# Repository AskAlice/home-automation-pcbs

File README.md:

# home-automation-pcbs

Open-hardware IoT boards for home automation, designed for **ESPHome** and/or
**Matter-over-Thread / Zigbee** (ESP32-C3/C6/S3/H2 based). All projects are
native **KiCad 8** and fully self-contained (project-local symbol libraries,
inline custom footprints, generator scripts — every file is reproducible).

> ⚠ **Verify before fabrication.** Footprints for ESP modules and sensors are
> drawn from published datasheets but these boards have not been through a
> physical run. v0.1 boards have signal routing left for autorouting
> (documented per-board). Check each board README before ordering PCBs.
> **RelayMini contains mains voltage — read its safety section first.**

## Boards

| Board | MCU | Ecosystem | Function | Status |
|---|---|---|---|---|
| [`boards/sensenode-c6`](boards/sensenode-c6) | ESP32-C6-WROOM-1 | ESPHome (Wi-Fi) + Matter/Thread | Temp/hum, lux, pressure, PIR | v0.1 routed (power), partial ratsnest |
| [`boards/presencepro-c3`](boards/presencepro-c3) | ESP32-C3-WROOM-02 | ESPHome | HLK-LD2410 mmWave presence + lux | v0.1 |
| [`boards/ledquad-c3`](boards/ledquad-c3) | ESP32-C3-WROOM-02 | ESPHome / WLED | 4-ch 12–24 V PWM LED driver | v0.1 |
| [`boards/relaymini-c3`](boards/relaymini-c3) | ESP32-C3-WROOM-02 | ESPHome | ⚠ Mains switch + BL0942 metering | v0.1, safety gates green |
| [`boards/ledhub-c6`](boards/ledhub-c6) | ESP32-C6-WROOM-1 | WLED / ESPHome | 2.8" TFT all-in-one LED controller | v0.1 (flagship) |
| [`boards/threadnode-h2`](boards/threadnode-h2) | ESP32-H2-MINI-1 | Matter-over-Thread / Zigbee | Battery contact sensor / button | v0.1 concept |
| [`boards/airquality-s3`](boards/airquality-s3) | ESP32-S3-WROOM-1 | ESPHome | CO₂ + VOC + temp/hum + OLED header | v0.1 concept |
| [`boards/blinddriver-c6`](boards/blinddriver-c6) | ESP32-C6-WROOM-1 | ESPHome / Matter | TMC2209 roller-blind controller | v0.1 concept |
| [`boards/irblaster-c3`](boards/irblaster-c3) | ESP32-C3-WROOM-02 | ESPHome | IR TX/RX climate bridge | v0.1 concept |
| [`boards/gardenprobe-c6`](boards/gardenprobe-c6) | ESP32-C6-WROOM-1 | ESPHome / Matter | Battery soil-moisture probe | v0.1 concept |
| [`boards/threadrcp-h2`](boards/threadrcp-h2) | ESP32-H2-MINI-1 | OpenThread RCP / Zigbee NCP | Border-router USB dongle | v0.1 concept |
| [`boards/garagepilot-c6`](boards/garagepilot-c6) | ESP32-C6-WROOM-1 | ESPHome | Garage-door relay + 3× inputs | v0.1 routed, DRC/ERC issues |

Each board folder contains: `*.kicad_pro/.kicad_sch/.kicad_pcb`, project-local
symbol library, `bom_lcsc.csv` (real, in-stock LCSC part numbers), `README.md`
(BOM, pinout, flashing, analyzer notes), `esphome/*.yaml`, render PNGs, and the
generator script (`gen_*.py`).

## Board showcase

### 🌡️ [SenseNode C6](boards/sensenode-c6) — environmental multisensor

One-per-room environmental node. ESP32-C6 gives you Wi-Fi 6 + BLE5 **and**
802.15.4, so the same SKU can run ESPHome today and Matter-over-Thread tomorrow.

- **Sensors:** SHT31 (temp/hum), BH1750 (lux), BMP280 (pressure), AM312 PIR (motion)
- **Power:** USB-C 5 V → AP2112K-3.3 LDO; EN/BOOT buttons; 1×4 prog header
- **Key parts:** ESP32-C6-WROOM-1, SHT31-AD1B, BH1750FVI, BMP280, AP2112K-3.3, USB-C 16P
- **Firmware:** `boards/sensenode-c6/esphome/sensenode-c6.yaml` (+ esp-matter note)

| Function | ESP32-C6 GPIO |
|---|---|
| I2C SDA / SCL (SHT31 + BH1750 + BMP280) | 6 / 7 |
| PIR OUT (J1) | 4 |
| Status LED (active low) | 8 |
| BOOT button | 9 |
| USB D− / D+ | 12 / 13 |
| UART0 TX0 / RX0 (prog header) | 16 / 17 |
| EN reset | EN |

---

### 🚶 [PresencePro C3](boards/presencepro-c3) — mmWave presence + lux

True still-presence detection (sitting at a desk, sleeping) where PIR fails,
with lux gating so automations only fire when it's dark.

- **Sensors:** HLK-LD2410(B) 24 GHz mmWave (moving + static targets, configurable
  gates), BH1750 ambient light
- **Power:** USB-C 5 V → AP2112K-3.3; native USB flashing
- **Key parts:** ESP32-C3-WROOM-02, HLK-LD2410B (module on 1×5 header), BH1750FVI, AP2112K
- **Firmware:** `esphome/presencepro-c3.yaml` (native `ld2410` component)

| Function | ESP32-C3 GPIO |
|---|---|
| Radar UART RX / TX | 4 / 5 |
| Radar OUT (occupancy) | 3 |
| I2C SDA / SCL (BH1750) | 6 / 7 |
| USB D− / D+ | 18 / 19 |
| Status LED | 10 |
| BOOT / EN | 9 / EN |
| UART0 RX0 / TX0 (prog) | 20 / 21 |

---

### 💡 [LEDQuad C3](boards/ledquad-c3) — 4-ch 12–24 V PWM LED driver

Analog RGBW strip driver for 12/24 V strips — the classic ESPHome `light.rgbw`
board, sized to hide behind furniture.

- **Outputs:** 4× AO3400A N-MOSFET low-side channels on 5.08 mm screw terminals
- **Power:** 12–24 V in (fused) → AP63205 buck 5 V/2 A → AP2112 3.3 V; USB-C
  programming diode-OR'd with the buck rail
- **Key parts:** ESP32-C3-WROOM-02, AP63205, AP2112K-3.3, 4× AO3400A, SS34, USB-C 16P
- **Firmware:** `esphome/ledquad-c3.yaml` (also WLED-friendly)

| Function | ESP32-C3 GPIO |
|---|---|
| PWM R / G / B / W | 4 / 5 / 6 / 7 |
| Status LED | 10 |
| BOOT button | 9 |
| USB D− / D+ | 18 / 19 |
| UART0 TX0 / RX0 | 21 / 20 |
| EN reset | EN |

---

### 🔌 [RelayMini C3](boards/relaymini-c3) — mains switch + energy metering

> ⚠ **110–240 VAC mains board. Lethal voltages. Qualified builders only —
> read the safety section in its README before anything else.**

Sonoff-Basic-class inline switch, but with proper engineering: fused input,
isolation slot, opto-isolated metering, and a SELV-side programming header.

- **Switching:** HF32F-G relay 10 A/250 VAC, 10 A fuse, MOV, creepage ≥ 6 mm,
  milled isolation slot between mains and SELV domains
- **Metering:** BL0942 (V/A/W/Wh/PF) with PC817 opto-isolated UART
- **Key parts:** ESP32-C3-WROOM-02, HLK-PM01 AC/DC, HF32F-G, BL0942, PC817 ×2
- **Firmware:** `esphome/relaymini-c3.yaml` (`bl0942` component)

| Function | GPIO |
|---|---|
| Relay driver (→ K1 coil) | GPIO6 |
| BL0942 UART RX / TX | GPIO4 / GPIO5 |
| User button (active low) | GPIO9 |
| Status LED (active low) | GPIO8 |
| Prog header (SELV side only!) TX0/RX0 | GPIO21 / GPIO20 |

---

### 🕹️ [LEDHub C6](boards/ledhub-c6) — all-in-one display LED controller (flagship)

A complete addressable-LED control station: status display, physical controls,
presence-aware switching and environmental telemetry, running **WLED** with a
custom usermod (`firmware/wled-usermod-ledhub`).

- **Display/UI:** 2.8" ILI9341 TFT (effect, palette, brightness, IP, RSSI),
  EC11 rotary encoder, 5-way nav buttons on one ADC pin (resistor ladder)
- **Sensors:** SHT31 + BH1750 (I2C), INMP441 I2S mic, LD2450 mmWave radar header
- **Output:** WS2812 data via 74AHCT125 level shifter + 470 Ω; separate 5 V LED
  power terminal
- **Key parts:** ESP32-C6-WROOM-1, 74AHCT125, INMP441, SHT31, BH1750, EC11, AP2112K
- **Firmware:** WLED usermod + `esphome/ledhub-c6.yaml`

| Function | ESP32-C6 GPIO |
|---|---|
| TFT SCK / MOSI / CS / DC / RST / BL | 6 / 7 / 5 / 4 / 1 / 2 |
| Encoder A / B | 15 / 16 |
| Nav button ladder (ADC) | 0 |
| INMP441 I2S SCK / WS / SD | 17 / 18 / 19 |
| I2C SDA / SCL | 20 / 21 |
| LD2450 radar RX / TX | 22 / 23 |
| WS2812 data (→ 74AHCT125) | 3 |
| USB D− / D+ | 12 / 13 |

---

### 🚪 [ThreadNode H2](boards/threadnode-h2) — battery Thread contact/button node

ESP32-H2 = 802.15.4 only, built for deep sleep: a CR2032 door/window sensor or
smart button on a Matter-over-Thread or Zigbee network.

- **Power:** CR2032 direct (no LDO — brown-out note in README); reed-switch
  deep-sleep wakeup
- **Key parts:** ESP32-H2-MINI-1, CR2032 holder, reed/header input, 4.7k I2C pull-ups
- **Firmware:** Matter-over-Thread via esp-matter (note in README)

| Signal | GPIO | Notes |
|---|---|---|
| REED | GPIO3 | reed switch to GND, deep-sleep wakeup |
| I2C SDA / SCL | GPIO12 / GPIO13 | expansion header |
| STAT LED | GPIO8 | pulse only — battery |
| BTN (BOOT) | GPIO9 | user button / ROM bootloader |
| TX0 / RX0 | GPIO24 / GPIO23 | prog header (no USB) |

---

### 🌫️ [AirQuality S3](boards/airquality-s3) — CO₂ / VOC / temp / humidity

Full indoor-air-quality node with photoacoustic CO₂ and metal-oxide VOC on one
I2C bus, plus a header for a 0.96" SSD1306 OLED readout.

- **Sensors:** Sensirion SCD40 (CO₂), SGP40 (VOC index), SHT40 (temp/hum)
- **Key parts:** ESP32-S3-WROOM-1, SCD40, SGP40, SHT40, AP2112K-3.3, USB-C
- **Firmware:** `esphome/airquality-s3.yaml` (`scd4x`, `sgp40`, `sht4x`)

| Signal | GPIO | Notes |
|---|---|---|
| I2C SDA / SCL | GPIO8 / GPIO9 | SCD40 0x62, SGP40 0x59, SHT40 0x44, OLED 0x3C |
| BOOT / RST | GPIO0 / EN | |
| STAT LED | GPIO38 | |
| USB D− / D+ | GPIO19 / GPIO20 | native USB flashing |
| TX0 / RX0 | GPIO43 / GPIO44 | spare UART |

---

### 🪟 [BlindDriver C6](boards/blinddriver-c6) — TMC2209 roller-blind controller

Quiet Trinamic stepper control for roller blinds, with ESPHome `cover`
semantics and Wi-Fi 6 + Thread on tap.

- **Driver:** TMC2209 socket (STEP/DIR/EN/DIAG + 1-wire UART config),
  end-stop header, 12 V VMOT with SS34 reverse-polarity protection
- **Power chain:** 12 V → AP63205 5 V → AP2112 3.3 V
- **Key parts:** ESP32-C6-WROOM-1, TMC2209, AP63205, screw terminals
- **Firmware:** `esphome/blinddriver-c6.yaml` (stepper cover)

| Signal | GPIO | Notes |
|---|---|---|
| STEP / DIR | GPIO4 / GPIO5 | TMC2209 socket |
| TMC_EN / DIAG | GPIO6 / GPIO7 | |
| TMC_UART | GPIO15 | 1-wire PDN_UART config |
| ENDSTOP | GPIO18 | header, pull-up |
| USB D− / D+ | GPIO12 / GPIO13 | |

---

### 📡 [IRBlaster C3](boards/irblaster-c3) — IR climate bridge

Give any dumb IR AC/heater a brain: ESPHome `climate_ir` with transmit and
receive (learn your remote's codes).

- **TX:** 2× TSAL6200 high-power IR LEDs driven by S8050 (GPIO4)
- **RX:** TSOP38238 38 kHz receiver (GPIO5); optional BH1750 lux on I2C
- **Key parts:** ESP32-C3-WROOM-02, TSAL6200 ×2, TSOP38238, S8050, BH1750
- **Firmware:** `esphome/irblaster-c3.yaml` (`remote_transmitter`/`remote_receiver`)

| Signal | GPIO | Notes |
|---|---|---|
| IR_TX | GPIO4 | → S8050 → 2× TSAL6200 |
| IR_RX | GPIO5 | TSOP38238 out |
| I2C SDA / SCL | GPIO6 / GPIO7 | BH1750 0x23 |
| STAT LED / BOOT | GPIO10 / GPIO9 | |
| USB D− / D+ | GPIO18 / GPIO19 | |

---

### 🌱 [GardenProbe C6](boards/gardenprobe-c6) — battery soil-moisture stick

Plant sensor built as a 70 × 25 mm stick: the probe is the PCB — a capacitive
copper area on the bottom tip, corrosion-free versus resistive probes.

- **Sensing:** capacitive fixed-RC probe (GPIO0/1), SHT31 on a load-switched
  rail (AO3401) to save battery, 100k/100k battery divider
- **Power:** 3.7 V LiPo on JST-PH, MCP1700-3302 LDO (charge externally)
- **Key parts:** ESP32-C6-WROOM-1, MCP1700, AO3401, SHT31
- **Firmware:** `esphome/gardenprobe-c6.yaml` (deep sleep)

| Signal | GPIO | Notes |
|---|---|---|
| SOIL_ADC / SOIL_CHG | GPIO0 / GPIO1 | capacitive probe |
| BATT_ADC | GPIO2 | Vbat/2 divider |
| LOAD_EN | GPIO3 | sensor rail load switch |
| I2C SDA / SCL | GPIO20 / GPIO21 | SHT31 0x44 |
| TX0 / RX0 | GPIO16 / GPIO17 | prog header (no USB) |

---

### 🧵 [ThreadRCP H2](boards/threadrcp-h2) — OpenThread border-router dongle

35 × 20 mm USB-C dongle that turns a Home Assistant box into an OpenThread
Border Router — the missing piece for all the H2/C6 Thread boards above.

- **Function:** ESP32-H2 RCP firmware (`esp_ot_br` / ot-rcp), native USB
  transport (GPIO26/27) — no UART bridge chip
- **Layout:** module rotated so the antenna overhangs the board edge
  (metal-free keep-out marked on silk)
- **Key parts:** ESP32-H2-MINI-1, USB-C 16P, AP2112K-3.3
- **Firmware:** Espressif ot_rcp example (flash command in README)

| Signal | GPIO | Notes |
|---|---|---|
| USB D− / D+ | GPIO26 / GPIO27 | RCP transport |
| STAT LED | GPIO8 | |
| BOOT / RST | GPIO9 / EN | |
| TX0 / RX0 | GPIO24 / GPIO23 | spare pads only |

### 🚗 [GaragePilot C6](boards/garagepilot-c6) — garage-door relay + 3× inputs

Dry-contact garage-door controller: ESP32-C6 closes a low-voltage relay across the opener's
wall-button terminals and reads door-closed / door-open reed switches plus a safety beam.
Powered from USB-C or a 5 V screw terminal.

- **Relay:** SRD-05VDC-SL-C SPDT dry contact (COM/NC/NO) via AO3400A MOSFET
- **Inputs:** 3× active-low digital inputs with 10 kΩ pull-ups for reed / safety sensors
- **Power:** USB-C 16P → AP2112K-3.3 LDO; auxiliary 5 V terminal
- **Key parts:** ESP32-C6-WROOM-1-N8, AP2112K-3.3, AO3400A, SRD-05VDC-SL-C, SS34 flyback
- **Firmware:** `boards/garagepilot-c6/esphome/garagepilot-c6.yaml` (`cover` template)

> ⚠ **v0.1 status:** routed and rendered, but KiCad DRC reports 96 violations / 23 unconnected
> items and ERC could not be run from the CLI.  See the board README before ordering PCBs.

| Function | ESP32-C6 GPIO |
|---|---|---|
| Relay driver | 4 |
| Door-closed / door-open / safety beam inputs | 5 / 6 / 7 |
| Status LED | 8 |
| BOOT / RESET buttons | 9 / EN |
| UART0 TX0 / RX0 (prog header) | 16 / 17 |

---

## Firmware

- `boards/*/esphome/*.yaml` — ready-to-adapt ESPHome configs.
- [`firmware/wled-usermod-ledhub`](firmware/wled-usermod-ledhub) — WLED usermod
  for LEDHub: ILI9341 status display, rotary encoder brightness, ADC-ladder
  nav buttons, LD2450 presence switching, SHT31/BH1750 telemetry.

## Part data

- [`datasheets/`](datasheets) — datasheet PDFs for all ICs/modules/connectors
  + `manifest.json` (re-sync: `python3 tools/fetch_datasheets.py`).
- [`3dmodels/`](3dmodels) — STEP + WRL models (KiCad packages3D, Espressif
  kicad-libraries, EasyEDA/LCSC) referenced from every PCB
  (`${KIPRJMOD}/../../3dmodels/…`) + `manifest.json` (the resolved model and
  transform per footprint; re-fetch + re-attach: `python3 tools/attach_3d.py`).

> **Note:** datasheet PDFs and STEP/WRL models are not committed to git — they
> are regenerable with `tools/fetch_datasheets.py` and `tools/attach_3d.py`.
> The render PNGs/GIFs in each board folder *are* committed so the READMEs
> display without any tooling.

## Tools

- `tools/kicadgen.py` — KiCad 8 s-expression writer + project validator used
  by every board generator (`python3 boards/<b>/gen_<b>.py` regenerates).
- `tools/render_pcb.py` — dependency-free PCB rasterizer (the render PNGs in
  each board folder).
- `tools/attach_3d.py` — fetches every footprint's 3D model (declarative
  footprint → source table) and rebuilds the `(model …)` blocks in all boards,
  aligning each body to the repo's custom footprint by pad bounding box.
  Needs `easyeda2kicad` (pip) for the LCSC parts.
- `tools/render3d.sh` — raytraced 3D renders (`render3d_top/bottom.png` per
  board) via `kicad-cli pcb render --quality high` (KiCad ≥ 9.0, 10.0.5
  known-good — CPU raytracer, no X server needed).
- `tools/turntable.sh` — 24-frame 360° orbit (`turntable.gif` per board) from
  the same raytracer, stitched with ffmpeg.

## Design rules

2-layer, 1.6 mm, 0.2 mm clearance, 0.25 mm min track, ≥0.5 mm power tracks,
GND pour on B.Cu, antenna keepouts on all RF modules. Every board passes
[kicad-happy](https://github.com/aklofas/kicad-happy) schematic/PCB analysis
with zero cross-net violations (DFM-001 = 0); remaining warnings are triaged
in each board's README.

## Acknowledgements

Validation and datasheet tooling: [kicad-happy](https://github.com/aklofas/kicad-happy)
(MIT, © 2025 Andrew Klofas). 3D models: EasyEDA/LCSC and the KiCad official
packages3D libraries. ESP module footprints verified against
[espressif/kicad-libraries](https://github.com/espressif/kicad-libraries).

## License

MIT — see [LICENSE](LICENSE).

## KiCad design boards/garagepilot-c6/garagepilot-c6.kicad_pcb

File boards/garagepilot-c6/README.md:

# GaragePilot C6 — ESP32-C6 garage-door controller

A compact, low-voltage garage-door opener controller built around the **ESP32-C6-WROOM-1** module.
The board provides a single dry relay contact for the opener's momentary-button circuit,
three isolated/digital inputs for door-closed / door-open reed switches and a safety beam,
USB-C power and programming, and a 5 V auxiliary screw terminal.
It is designed for **ESPHome** (and can be adapted for Matter-over-Thread later because the
C6 includes an 802.15.4 radio).

> **Status: v0.1 prototype — not production-ready.**
> The board has been placed, autorouted, and visually inspected, but KiCad DRC still reports
> 96 clearance violations and 23 unconnected items (see Validation below).  Do not order panels
> without first resolving these.

## What it does

* Closes a **dry SPDT relay contact** across the garage-door opener's wall-button terminals
  (`COM` / `NO`) for a configurable pulse (typically 250 ms).
* Reads **three active-low digital inputs** with onboard 10 kΩ pull-ups:
  * `INPUT1` — door-closed reed / limit switch
  * `INPUT2` — door-open reed / limit switch
  * `INPUT3` — safety beam / obstruction sensor
* Powers the logic from **USB-C** or a **5 V auxiliary terminal**, regulated down to 3.3 V.
* Exposes a **1×4 2.54 mm programming header** (3.3 V, TX0, RX0, GND) and a **BOOT** + **RESET**
  tactile button pair for firmware flashing.
* Provides test points for +5 V, +3.3 V, GND, and the relay-driver signal.

## Frozen pin map

| Function | ESP32-C6 GPIO | Net / connector |
|---|---|---|
| Relay driver (active high) | IO4 | `RELAY_DRV` → Q1 → K1 coil |
| Door-closed input (pull-up, active low) | IO5 | `INPUT1` on J3 pin 1 |
| Door-open input (pull-up, active low) | IO6 | `INPUT2` on J3 pin 2 |
| Safety beam input (pull-up, active low) | IO7 | `INPUT3` on J3 pin 3 |
| Status LED (active high) | IO8 | D2 red LED |
| BOOT button | IO9 | SW2 (shared with ROM bootloader) |
| RESET button | EN | SW1 |
| USB D− | IO12 | J1 via 22 Ω series resistor |
| USB D+ | IO13 | J1 via 22 Ω series resistor |
| UART0 TX (prog header) | IO16 | J5 pin 2 |
| UART0 RX (prog header) | IO17 | J5 pin 3 |

## Key parts / BOM summary

Full BOM with LCSC numbers and sourcing URLs is in [`bom_lcsc.csv`](bom_lcsc.csv).

| Designator | Value / MPN | Footprint | Purpose |
|---|---|---|---|
| U1 | ESP32-C6-WROOM-1-N8 | Custom module | MCU + Wi-Fi 6 + BLE + 802.15.4 |
| U2 | AP2112K-3.3TRG1 | SOT-23-5 | 3.3 V / 600 mA LDO |
| Q1 | AO3400A | SOT-23 | Relay-coil low-side N-MOSFET |
| K1 | SRD-05VDC-SL-C | T73 / SRD | 5 V SPDT relay, 10 A contact |
| D1 | SS34 | SMA | Flyback diode for relay coil |
| D2 | LTST-C190KRKT | 0603 red LED | Status LED |
| J1 | TYPE-C-31-M-12 | USB-C 16P mid-mount | USB-C power + flashing |
| J2 | WJ500V-5.08-3P | 3P 5.08 mm screw terminal | Relay COM/NC/NO |
| J3 | WJ500V-5.08-3P | 3P 5.08 mm screw terminal | Inputs 1–3 |
| J4 | WJ500V-5.08-2P | 2P 5.08 mm screw terminal | AUX +5 V / GND |
| J5 | KH-2.54PH180-1X4P-L13.5 | 1×4 2.54 mm header | Programming / UART |
| SW1, SW2 | TS-1187A-B-A-B | 6×6 mm SMD tactile | RESET, BOOT |
| R1, R3–R5, R10–R11 | 10 kΩ 0603 | Pull-ups for LED, inputs, EN, BOOT |
| R2 | 100 Ω 0603 | Gate damping resistor for Q1 |
| R6, R7 | 4.7 kΩ 0603 | USB Type-C CC pulldowns |
| R8, R9 | 22 Ω 0603 | USB D+/D− series resistors |
| C1, C2 | 10 µF 0603 | VBUS and +3V3 bulk |
| C3 | 100 nF 0603 | +3V3 decoupling |

## Design calculations

**LDO power budget (AP2112K-3.3)**

* Maximum dropout at 600 mA: ~350 mV typical; with 5 V input the headroom is comfortable.
* Expected module load: ESP32-C6 peak TX current ≈ 400 mA at 3.3 V (from Espressif datasheet).
  The LDO is rated 600 mA and is sized with modest margin; keep USB-C / 5 V source resistance low.
* LDO power dissipation at peak: `(5 V − 3.3 V) × 0.4 A ≈ 0.68 W`.  The SOT-23-5 thermal pad is
  small, so continuous high-current TX should be thermally validated on the prototype.

**Relay coil drive**

* SRD-05VDC-SL-C coil: ≈ 70 Ω → coil current `5 V / 70 Ω ≈ 71 mA`.
* AO3400A Rds(on) at Vgs = 3.3 V: ≈ 25 mΩ typical.  MOSFET dissipation is negligible.
* Flyback diode D1 (SS34, 3 A / 40 V) provides a safe recirculation path.
* Gate resistor R2 (100 Ω) limits ringing without noticeably slowing the 250 ms pulse.

**USB-C CC detection**

* R6 / R7 = 4.7 kΩ each pull CC1 / CC2 to GND, telling a Type-C source to supply 5 V at
  default current.  These are placed near the connector.

**Input pull-ups**

* R3/R4/R5 = 10 kΩ.  With a reed switch to GND, input current is `3.3 V / 10 kΩ = 0.33 mA`.
  This is a good compromise between noise immunity and battery-friendliness if the auxiliary
  supply is modest.

## Fabrication notes

* **Layers:** 2-layer, 1.6 mm, 1 oz copper, ENIG or lead-free HASL.
* **Clearances:** design rules are 0.2 mm track/clearance, 0.6 mm via / 0.3 mm drill.
  The autorouter was configured with 0.25 mm clearance to improve yield.
* **RF keepout:** the ESP32-C6-WROOM-1 PCB antenna sits at the **bottom** of the module.
  A copper keepout zone forbids tracks, vias, pours, and copper polygons underneath it on all
  copper layers.  Do not place tall metal components or traces in this area.
* **Mounting:** four M2.5 non-plated mounting holes, inset 10 mm from board edges on a
  100 mm × 60 mm board.
* **Programming:** hold BOOT (SW2) while pressing RESET (SW1), or use the `esphome` USB
  upload workflow once the initial flash is complete.
* **5 V auxiliary terminal (J4):** provides a convenient way to power the board from an
  existing 5 V supply inside the opener enclosure.  USB-C and J4 are diode-less, so do not
  connect both at the same time unless both sources are safely OR'd externally.
* **Relay terminals (J2):** dry contact only — these carry the low-voltage momentary-button
  circuit from the opener, not mains voltage.  Verify your opener's control voltage stays
  within the relay/contact rating (10 A / 30 VDC / 125 VAC max per SRD datasheet).

## Firmware

A starter ESPHome configuration is provided in
[`esphome/garagepilot-c6.yaml`](esphome/garagepilot-c6.yaml).
It exposes:

* a `cover` entity for the garage door,
* binary sensors for `Door Closed`, `Door Open`, and `Safety Beam`,
* a `Status LED` light,
* a `Restart` button, and
* on-board BOOT button mapped to `cover.toggle`.

Update the `!secret` placeholders before flashing.

## Validation

### Schematic / ERC

KiCad CLI ERC **could not be run**:

```bash
kicad-cli sch erc --format report --output erc_report.rpt garagepilot-c6.kicad_sch
```

Both the native KiCad 8 `.kicad_sch` and a backported KiCad 9 `.kicad_sch` failed to load
with the error `Failed to load schematic` (exit code 3).  This appears to be a KiCad CLI /
generator-version compatibility issue in this workspace, not a missing library file.  ERC
must be performed manually in KiCad's schematic editor until the CLI load failure is resolved.

### PCB / DRC

```bash
cd boards/garagepilot-c6
kicad-cli pcb drc --format report --output routed_drc_report.rpt garagepilot-c6.kicad_pcb
```

Result:

```text
Found 96 DRC violations
Found 23 unconnected items
Found 0 Footprint errors
Found 0 shorting items
Found 0 items not allowed
Found 0 courtyards overlap
Saved DRC Report to routed_drc_report.rpt
```

The remaining issues are:

* **Clearance violations** between autorouted tracks/vias on B.Cu and F.Cu (actual clearances
  down to ~0.075 mm in a few places, below the 0.2 mm rule).
* **Unconnected items** — mostly missing copper connections for VBUS stitching, the relay coil
  path, and a few signal pads that the autorouter did not complete.
* A number of **library footprint mismatch / missing-library warnings**.  These are caused by
  standard KiCad footprints embedded in the board not matching the system's installed KiCad
  library versions, plus the project pinning a non-existent footprint library name.

There are **no shorting items, no courtyard overlaps, and no disallowed items**.
The v0.1 board is therefore documented as routed but **not DRC-clean**.

### 3D models / renders

* All referenced STEP models are present in [`3dmodels/`](3dmodels/) and listed in
  [`3dmodels/MANIFEST.md`](3dmodels/MANIFEST.md) with source URLs, licenses, and SHA-256
  checksums.
* Renders were produced with:

```bash
kicad-cli pcb render -w 1600 -h 1200 --side top --quality high --perspective --rotate=330,330,0 -o images/render3d_top.png garagepilot-c6.kicad_pcb
kicad-cli pcb render -w 1600 -h 1200 --side bottom --quality high --perspective --rotate=210,30,0 -o images/render3d_bottom.png garagepilot-c6.kicad_pcb
kicad-cli pcb render -w 1600 -h 1200 --side top --quality high -o images/render_top.png garagepilot-c6.kicad_pcb
```

The populated SMD models (ESP32 module, relay, USB-C, terminals, passives) are visible in the
renders and were inspected for floating / rotated / badly-scaled geometry.

## Regenerating the project

```bash
python3 boards/garagepilot-c6/gen_garagepilot_c6.py
```

This recreates the project-local symbol library, schematic, and PCB placement.  The copper
is intentionally left unrouted in the generator so the board can be exported to Specctra DSN
and autorouted (see the generator comments for the freeroute pipeline used for v0.1).

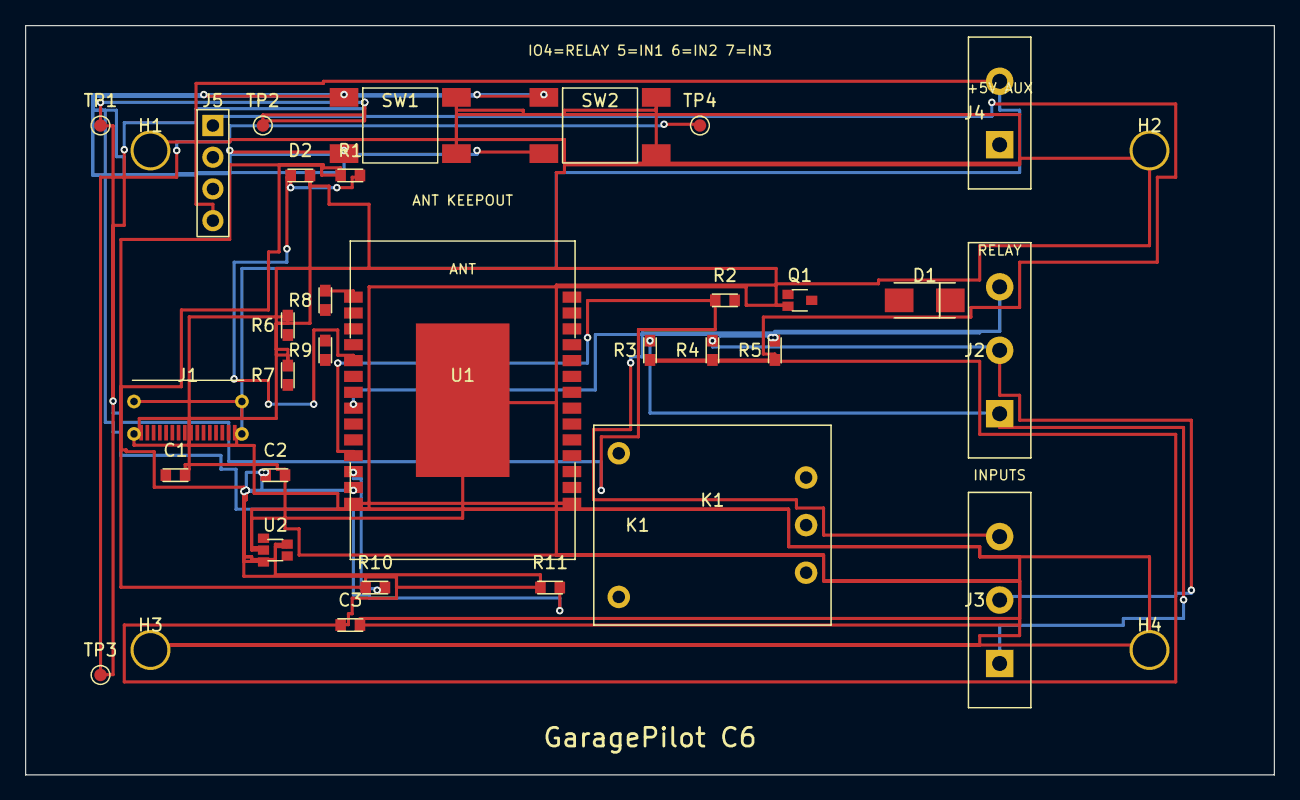
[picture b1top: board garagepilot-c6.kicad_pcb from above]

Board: 2 copper layers, 100.0 x 60.0 mm, 35 parts (0 on the bottom side), 21 nets.

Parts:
C1, C2: 10uF; C_0603_1608Metric
C3: 100nF; C_0603_1608Metric
D1: SS34; D_SMA
D2: LED_RED; LED_0603_1608Metric
H1, H2, H3, H4: MountingHole_M2.5
J1: USB_C_16P; USB_C_Receptacle_USB2.0_16P
J2: RELAY; ScrewTerm-5.08-3P
J3: INPUTS; ScrewTerm-5.08-3P
J4: AUX_5V; ScrewTerm-5.08-2P
J5: PROG; PinHeader_1x04_P2.54mm_Vertical
K1: SRD-05VDC-SL-C; Relay_T73
Q1: AO3400A; SOT-23
R1, R3, R4, R5, R10, R11: 10k; R_0603_1608Metric
R2: 100R; R_0603_1608Metric
R6, R7: 4.7k; R_0603_1608Metric
R8, R9: 22R; R_0603_1608Metric
SW1: RESET; Tactile-6x6-SMD
SW2: BOOT; Tactile-6x6-SMD
TP1: +5V; TestPoint_Pad_1.0mm
TP2: +3V3; TestPoint_Pad_1.0mm
TP3: GND; TestPoint_Pad_1.0mm
TP4: RELAY_DRV; TestPoint_Pad_1.0mm
U1: ESP32-C6-WROOM-1-N8; ESP32-C6-WROOM-1
U2: AP2112K-3.3; SOT-23-5

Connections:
+3V3: C2.1, C3.1, J5.1, R1.1, R3.1, R4.1, R5.1, R10.1, R11.1, U1.2, U2.3, U2.5
+5V: D1.1, J4.1, K1.1
BOOT: R11.2, SW1.1, SW1.3, SW2.1, SW2.3, U1.15
EN: R10.2, U1.3
GND: C1.2, C2.2, C3.2, D2.2, J1.1, J1.8, J1.9, J1.16, J1.S1, J1.S2, J1.S3, J1.S4, J4.2, J5.4, Q1.2, R6.2, R7.2, SW1.2, SW1.4, SW2.2, SW2.4, U1.1, U1.28, U1.29, U2.2
INPUT1: J2.1, J3.1, R3.2, U1.5
INPUT2: J2.2, J3.2, R4.2, U1.6
INPUT3: J2.3, J3.3, R5.2, U1.7
K1_COIL_P: D1.2, K1.2, Q1.3
LED1_A: D2.1, R1.2, U1.10
Q1_GATE: Q1.1, R2.2
RELAY_DRV: R2.1, TP1.1, TP2.1, TP3.1, TP4.1, U1.4
RX0: J5.3, U1.24
TX0: J5.2, U1.25
USB_CC1: J1.3, R6.1
USB_CC2: J1.14, R7.1
USB_DM: J1.5, J1.12, R9.1
USB_DM_FILT: R9.2, U1.13
USB_DP: J1.4, J1.13, R8.1
USB_DP_FILT: R8.2, U1.14
VBUS: C1.1, J1.2, J1.7, J1.10, J1.15, U2.1

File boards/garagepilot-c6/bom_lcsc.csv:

Designator,Qty,Value,Footprint,MPN,LCSC,Description,Datasheet_URL,Sourcing_URL
"U1",1,"ESP32-C6-WROOM-1-N8","garagepilot-c6-lib:ESP32-C6-WROOM-1","ESP32-C6-WROOM-1-N8","C5366877","Espressif Wi-Fi 6 / BLE / 802.15.4 module","https://www.espressif.com/sites/default/files/documentation/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","https://lcsc.com/product-detail/C5366877.html"
"U2",1,"AP2112K-3.3","Package_TO_SOT_SMD:SOT-23-5","AP2112K-3.3TRG1","C51115","LDO 3.3 V 600 mA","https://www.diodes.com/assets/Datasheets/AP2112.pdf","https://lcsc.com/product-detail/C51115.html"
"Q1",1,"AO3400A","Package_TO_SOT_SMD:SOT-23","AO3400A","C20917","N-channel MOSFET 30 V 5.7 A","https://www.lcsc.com/datasheet/lcsc_datasheet_2304140030_AOS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","https://lcsc.com/product-detail/C20917.html"
"K1",1,"SRD-05VDC-SL-C","garagepilot-c6-lib:Relay_T73","SRD-05VDC-SL-C","C95269","5 V SPDT relay 10 A","https://www.lcsc.com/datasheet/lcsc_datasheet_2304140030_SON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","https://lcsc.com/product-detail/C95269.html"
"D1",1,"SS34","Diode_SMD:D_SMA","SS34","C8678","Schottky diode 40 V 3 A flyback","https://www.lcsc.com/datasheet/lcsc_datasheet_2304140030_Gua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","https://lcsc.com/product-detail/C8678.html"
"D2",1,"LED red 0603","LED_SMD:LED_0603_1608Metric","LTST-C190KRKT","C2286","Red status LED","~","https://lcsc.com/product-detail/C2286.html"
"R1,R3,R4,R5,R10,R11",6,"10k","Resistor_SMD:R_0603_1608Metric","0603WAF1002T5E","C25804","Resistor 10 kΩ 0603 1%","~","https://lcsc.com/product-detail/C25804.html"
"R2",1,"100R","Resistor_SMD:R_0603_1608Metric","RCA03100RFLF","C22369795","Resistor 100 Ω 0603 1% gate","~","https://lcsc.com/product-detail/C22369795.html"
"R6,R7",2,"4.7k","Resistor_SMD:R_0603_1608Metric","0603WAF4701T5E","C23162","Resistor 4.7 kΩ 0603 1% CC pulldown","~","https://lcsc.com/product-detail/C23162.html"
"R8,R9",2,"22R","Resistor_SMD:R_0603_1608Metric","0603WAF220JT5E","C22926","Resistor 22 Ω 0603 5% USB series","~","https://lcsc.com/product-detail/C22926.html"
"C1,C2",2,"10uF","Capacitor_SMD:C_0603_1608Metric","CL10A106KP8NNNC","C15849","MLCC 10 µF 6.3 V X5R 0603","~","https://lcsc.com/product-detail/C15849.html"
"C3",1,"100nF","Capacitor_SMD:C_0603_1608Metric","0603B104K500NT","C14663","MLCC 100 nF 50 V X7R 0603","~","https://lcsc.com/product-detail/C14663.html"
"SW1,SW2",2,"TS-1187A","garagepilot-c6-lib:Tactile-6x6-SMD","TS-1187A-B-A-B","C139797","6x6 mm SMD tactile switch","~","https://lcsc.com/product-detail/C139797.html"
"J1",1,"TYPE-C-31-M-12","Connector_USB:USB_C_Receptacle_USB2.0_16P","TYPE-C-31-M-12","C165948","USB-C 2.0 16-pin mid-mount receptacle","https://www.lcsc.com/datasheet/lcsc_datasheet_2410252104_Kor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","https://lcsc.com/product-detail/C165948.html"
"J2,J3",2,"WJ500V-5.08-3P","garagepilot-c6-lib:ScrewTerm-5.08-3P","WJ500V-5.08-3P","C8465","5.08 mm 3-pin screw terminal","~","https://lcsc.com/product-detail/C8465.html"
"J4",1,"WJ500V-5.08-2P","garagepilot-c6-lib:ScrewTerm-5.08-2P","WJ500V-5.08-2P","C8465","5.08 mm 2-pin screw terminal","~","https://lcsc.com/product-detail/C8465.html"
"J5",1,"KH-2.54PH180-1X4P-L13.5","Connector_PinHeader_2.54mm:PinHeader_1x04_P2.54mm_Vertical","KH-2.54PH180-1X4P-L13.5","C49258","1x4 2.54 mm programming header","~","https://lcsc.com/product-detail/C49258.html"
"TP1-TP4",4,"Test point","garagepilot-c6-lib:TestPoint_Pad_1.0mm","Test point","C152136","1.0 mm round SMD test point","~","https://lcsc.com/product-detail/C152136.html"
"H1-H4",4,"MountingHole_M2.5","garagepilot-c6-lib:MountingHole_M2.5","—","—","M2.5 non-plated mounting hole","~","~"

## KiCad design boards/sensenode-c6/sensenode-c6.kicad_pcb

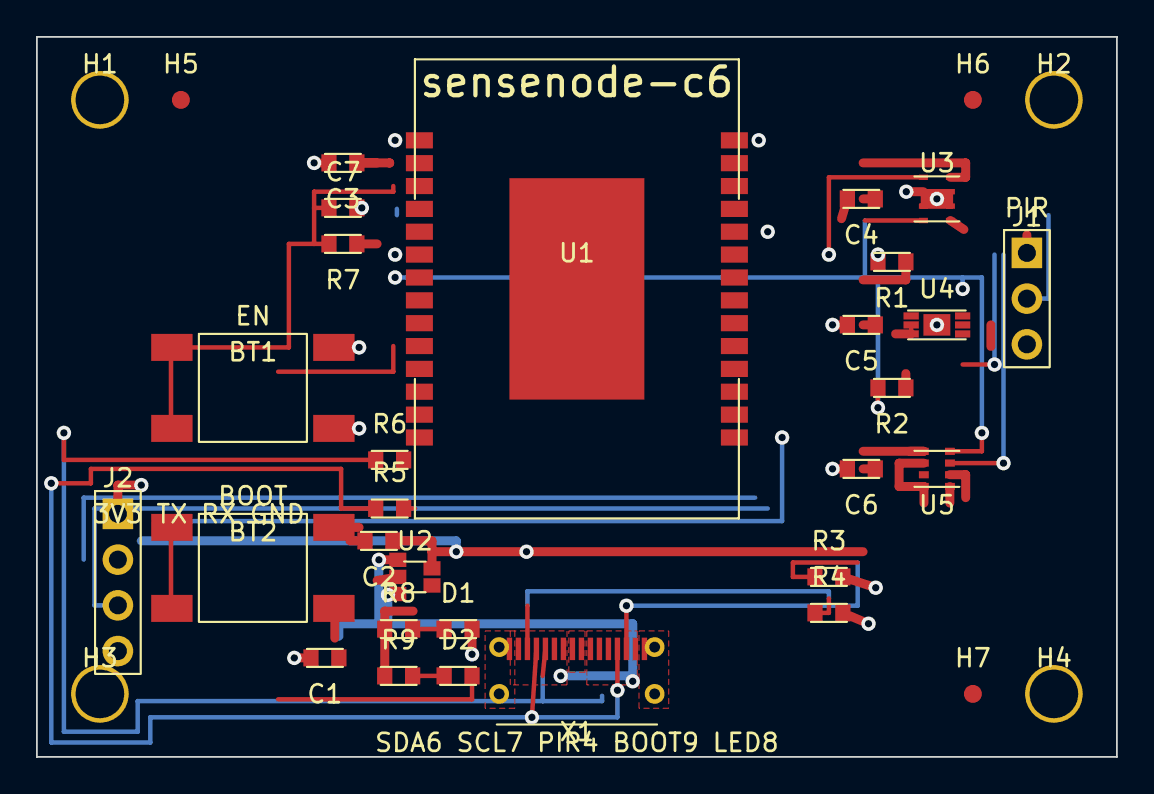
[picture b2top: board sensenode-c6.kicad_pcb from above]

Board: 2 copper layers, 60.0 x 40.0 mm, 35 parts (0 on the bottom side), 19 nets.

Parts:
BT1, BT2: SW_PUSH; Tactile-6x6-SMD
C1, C2: 10uF; C_0603_1608Metric
C3, C4, C5, C6, C7: 100nF; C_0603_1608Metric
D1: LED_RED; LED_0603_1608Metric
D2: LED_GRN; LED_0603_1608Metric
H1, H2, H3, H4: MountingHole_M2.5
H5, H6, H7: Fiducial; Fiducial_1mm
J1: Conn_01x03; PinHeader_1x03_P2.54mm_Vertical
J2: Conn_01x04; PinHeader_1x04_P2.54mm_Vertical
R1, R2: 4.7k; R_0603_1608Metric
R3, R4: 5.1k; R_0603_1608Metric
R5, R6: 22R; R_0603_1608Metric
R7: 10k; R_0603_1608Metric
R8, R9: 1k; R_0603_1608Metric
U1: ESP32-C6-WROOM-1
U2: AP2112K-3.3; SOT-23-5
U3: SHT31; SHT31-DFN8
U4: BH1750; BH1750-WSOF6
U5: BMP280; BMP280-LGA8
X1: USB_C_16P; USB_C_Receptacle_USB2.0_16P

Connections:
+3V3: C2.1, C3.1, C4.1, C5.1, C6.1, J1.1, J2.1, R1.1, R2.1, R7.1, R8.1, R9.1, U1.2, U2.5, U3.5, U4.1, U4.5, U5.2, U5.6, U5.8
BOOT: BT1.1, BT1.3, BT2.1, BT2.3, U1.15
EN: C7.1, R7.2, U1.3
GND: BT1.2, BT1.4, BT2.2, BT2.4, C1.2, C2.2, C3.2, C4.2, C5.2, C6.2, C7.2, D1.2, J1.3, J2.4, R3.2, R4.2, U1.1, U1.28, U1.29, U2.2, U3.2, U3.8, U3.9, U4.2, U4.3, U4.7, U5.1, U5.5, U5.7, X1.1, X1.8, X1.9, X1.16, X1.S1, X1.S2, X1.S3, X1.S4
I2C_SCL: R2.2, U1.7, U3.4, U4.6, U5.4
I2C_SDA: R1.2, U1.6, U3.1, U4.4, U5.3
LED1_A: D1.1, R8.2
LED2_A: D2.1, R9.2
PIR_OUT: J1.2, U1.4
RX0: J2.3, U1.24
STAT_LED: D2.2, U1.10
TX0: J2.2, U1.25
USB_CC1: R3.1, X1.3
USB_CC2: R4.1, X1.14
USB_DM: R6.2, U1.13
USB_DM_CON: R6.1, X1.5, X1.12
USB_DP: R5.2, U1.14
USB_DP_CON: R5.1, X1.4, X1.13
VBUS: C1.1, U2.1, U2.3, X1.2, X1.7, X1.10, X1.15

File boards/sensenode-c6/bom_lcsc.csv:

Ref,Value,Footprint,LCSC,MPN,Qty
U1,ESP32-C6-WROOM-1,custom:ESP32-C6-WROOM-1,C32020546,ESP32-C6-WROOM-1-N8,1
X1,USB_C_16P,Connector_USB:USB_C_Receptacle_USB2.0_16P,C165948,TYPE-C-31-M-12,1
U2,AP2112K-3.3,Package_TO_SOT_SMD:SOT-23-5,C51115,AP2112K-3.3TRG1,1
U3,SHT31,custom:SHT31-DFN8,C194656,SHT31-DIS-B2.5kS,1
U4,BH1750,custom:BH1750-WSOF6,C78960,BH1750FVI-TR,1
U5,BMP280,custom:BMP280-LGA8,C92466,BMP280,1
R1,4.7k,Resistor_SMD:R_0603_1608Metric,C23162,0603WAF4701T5E,1
R2,4.7k,Resistor_SMD:R_0603_1608Metric,C23162,0603WAF4701T5E,1
R3,5.1k,Resistor_SMD:R_0603_1608Metric,C23186,0603WAF5101T5E,1
R4,5.1k,Resistor_SMD:R_0603_1608Metric,C23186,0603WAF5101T5E,1
R5,22R,Resistor_SMD:R_0603_1608Metric,C22926,0603WAF220JT5E,1
R6,22R,Resistor_SMD:R_0603_1608Metric,C22926,0603WAF220JT5E,1
R7,10k,Resistor_SMD:R_0603_1608Metric,C25804,0603WAF1002T5E,1
R8,1k,Resistor_SMD:R_0603_1608Metric,C21190,0603WAF1001T5E,1
R9,1k,Resistor_SMD:R_0603_1608Metric,C21190,0603WAF1001T5E,1
C1,10uF,Capacitor_SMD:C_0603_1608Metric,C15849,CL10A106KP8NNNC,1
C2,10uF,Capacitor_SMD:C_0603_1608Metric,C15849,CL10A106KP8NNNC,1
C3,100nF,Capacitor_SMD:C_0603_1608Metric,C14663,0603B104K500NT,1
C4,100nF,Capacitor_SMD:C_0603_1608Metric,C14663,0603B104K500NT,1
C5,100nF,Capacitor_SMD:C_0603_1608Metric,C14663,0603B104K500NT,1
C6,100nF,Capacitor_SMD:C_0603_1608Metric,C14663,0603B104K500NT,1
C7,100nF,Capacitor_SMD:C_0603_1608Metric,C14663,0603B104K500NT,1
D1,LED_RED,LED_SMD:LED_0603_1608Metric,C2286,LTST-C190KRKT,1
D2,LED_GRN,LED_SMD:LED_0603_1608Metric,C2297,LTST-C190KGKT,1
BT1,SW_PUSH,custom:Tactile-6x6-SMD,C139797,TS-1187A-B-A-B,1
BT2,SW_PUSH,custom:Tactile-6x6-SMD,C139797,TS-1187A-B-A-B,1
J1,Conn_01x03,Connector_PinHeader_2.54mm:PinHeader_1x03_P2.54mm_Vertical,C49257,KH-2.54PH180-1X3P-L13.5,1
J2,Conn_01x04,Connector_PinHeader_2.54mm:PinHeader_1x04_P2.54mm_Vertical,C49258,KH-2.54PH180-1X4P-L13.5,1

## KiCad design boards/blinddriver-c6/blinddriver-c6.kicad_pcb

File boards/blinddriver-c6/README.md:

# blinddriver-c6 — TMC2209 roller-blind controller (SPEC 7.3)

ESP32-C6-WROOM-1 driving a TMC2209 stepper socket for a roller blind:
12 V VMOT input (SS34 reverse-polarity protection), AP63205 buck to 5 V,
AP2112 to 3.3 V, screw terminals for motor + VMOT, end-stop header.
**v0.1 concept board.**

- Board: 60 × 40 mm, 2-layer, USB-C bottom edge
- Status: `python3 boards/wave2/wave2gen.py blinddriver-c6` → self-check OK

## BOM (bom_lcsc.csv)

| Ref | Value | Footprint | LCSC # | MPN | Qty |
|---|---|---|---|---|---|
| U1 | ESP32-C6-WROOM-1 | ESP32-C6-WROOM-1 | C2946979 | ESP32-C6-WROOM-1-N8 | 1 |
| U2 | AP63205 (buck 12V→5V) | SOT-23-6 | C2677326 | AP63205WU-7 | 1 |
| U3 | AP2112K-3.3 | SOT-23-5 | C51118 | AP2112K-3.3TRG1 | 1 |
| U4 | TMC2209 module | custom:TMC2209-Socket (J3/J4) | C3137092 | TMC2209 | 1 |
| L1 | 4.7uH | custom:Inductor-4x4 | C424814 | SWPA4026S4R7MT | 1 |
| D1 | LED red (STAT) | 0603 | C2286 | 17-21SURC/S530-A3/TR8 | 1 |
| D2 | SS34 (VMOT reverse pol.) | SMA | C14936 | SS34 | 1 |
| D3 | SS34 (buck catch) | SMA | C14936 | SS34 | 1 |
| X1 | USB-C 16P | custom:USB-C-16P-MidMount | C165948 | TYPE-C-31-M-12 | 1 |
| BT1,BT2 | SW_PUSH (BOOT / RST) | custom:Tactile-6x6-SMD | C91808 | TS-1187A-B-A-B | 2 |
| R8 | 1k | 0603 | C21190 | 0603WAF1001T5E | 1 |
| R1,R2,R9 | 5.1k (CC/USB) | 0603 | C23186 | 0603WAF5101T5E | 3 |
| R3,R4 | 22R (USB series) | 0603 | C25076 | 0603WAF220JT5E | 2 |
| R7 | 10k (EN) | 0603 | C98252 | 0603WAF1002T5E | 1 |
| R10,R11 | 100k (buck FB) | 0603 | C98258 | 0603WAF1003T5E | 2 |
| C1–C7 | 100nF | 0603 | C14663 | CL10B104KB8NNNC | 7 |
| C8 | 100uF (VMOT bulk) | custom:CP-Elec-6.3x5.4 | C145465 | RVT1H101M0607 | 1 |
| J5 | VMOT_IN screw 1x02 | custom:ScrewTerm-5.08-2P | C8464 | KF128-5.08-2P | 1 |
| J6,J7 | MOT_A / MOT_B screw 1x02 | custom:ScrewTerm-5.08-2P | C8464 | KF128-5.08-2P | 2 |
| J8 | Conn_01x03 (3V3/ENDSTOP/GND) | PinHeader_1x03_P2.54mm | C49240 | A2541WV-3P | 1 |

## Pinout (C6-WROOM-1)

| Signal | GPIO | Notes |
|---|---|---|
| STEP / DIR | GPIO4 / GPIO5 | to TMC2209 socket |
| TMC_EN | GPIO6 | low = driver enabled |
| DIAG | GPIO7 | TMC2209 diagnostic output |
| TMC_UART | GPIO15 | 1-wire UART config (PDN_UART) |
| ENDSTOP | GPIO18 | J8 header, pull-up |
| STAT_LED | GPIO1 | D1 via R8 |
| BOOT | GPIO0 | BT1; RST = EN (BT2) |
| USB D- / D+ | GPIO12 / GPIO13 | via 22R R3/R4, native USB flashing |
| TX0 / RX0 | GPIO16 / GPIO17 | spare |

## Firmware

See `esphome/blinddriver-c6.yaml` — stepdir stepper + time_based cover,
end-stop binary sensor, driver-enable switch, TMC2209 UART note.

## Routing status

**v0.1 concept — signals left for autorouting.** Power rails routed
(VMOT/12V/+5V/+3V3/GND, 0.5 mm power width, GND stitching); STEP/DIR/UART/
DIAG/end-stop signals unrouted.

## Analyzer notes

`analyze_pcb.py`: **DFM-001 = 0**. RT-001 unrouted errors expected.
STAT_LED was unassigned in the original plan — now on GPIO1.

## Caveats (verify before fabrication!)

- 12 V VMOT: check SS34 orientation (D2 input, D3 buck catch) and C8
  ripple rating for your motor current.
- TMC2209 socket pinout follows the common StepStick order — verify
  against your module (there are two header orientations).
- Buck feedback R10/R11 100k/100k sets 5 V via AP63205 reference — verify
  ratio against datasheet before fab.
- **Verify all footprints, pin numbers, and clearances against KiCad
  libraries + datasheets before ordering boards.**

## Renders

| Raytraced 3D (KiCad) | 2D layout |
|---|---|
|  |  |
|  |  |

🎬 24 real KiCad raytraced frames stitched with ffmpeg (tools/turntable.sh).

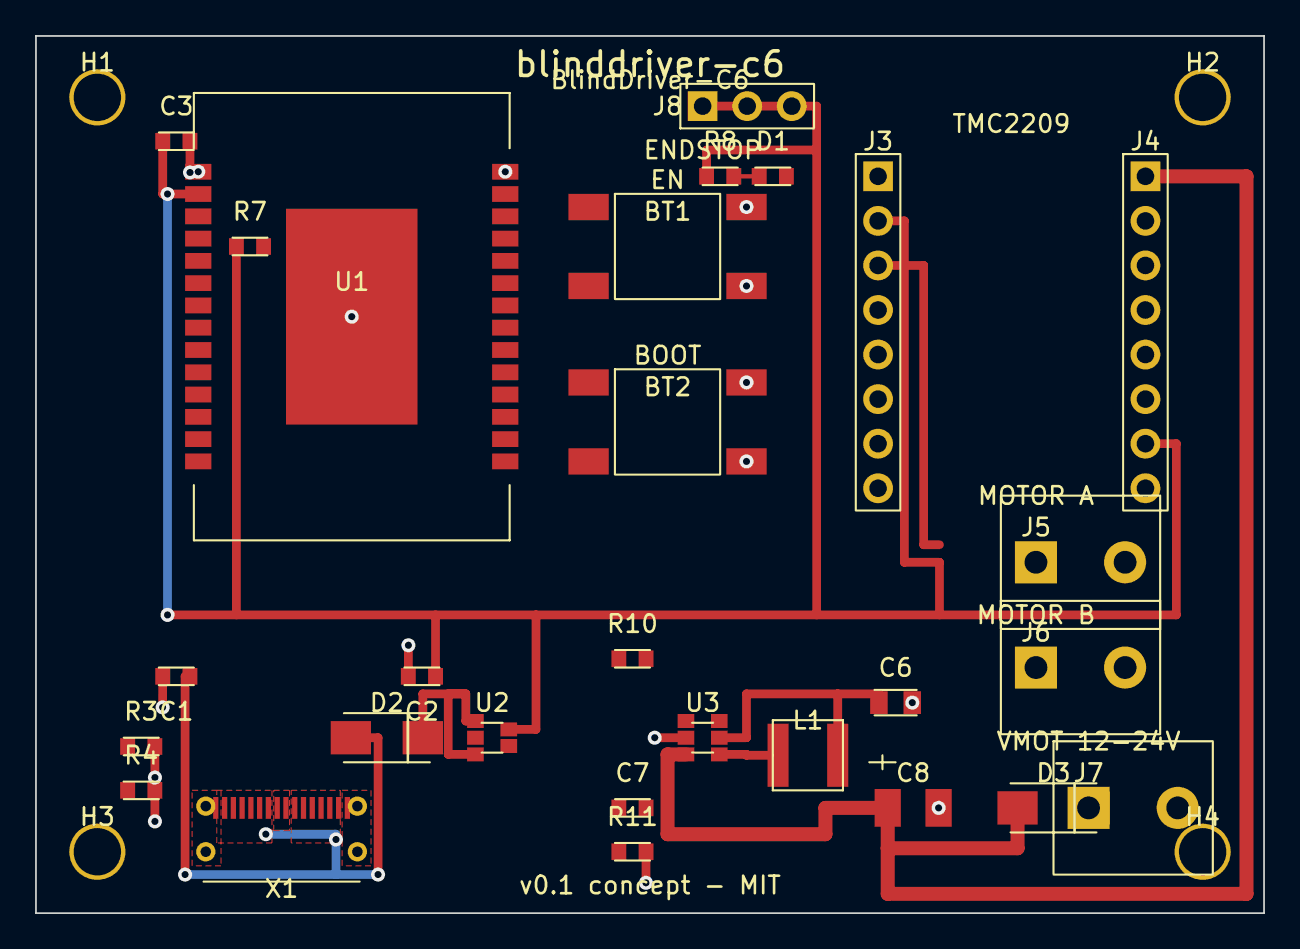
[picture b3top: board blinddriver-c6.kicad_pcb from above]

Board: 2 copper layers, 70.0 x 50.0 mm, 32 parts (0 on the bottom side), 24 nets.

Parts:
BT1, BT2: SW_PUSH; Tactile-6x6-SMD
C1, C2: 10uF; C_0603_1608Metric
C3, C7: 100nF; C_0603_1608Metric
C6: 22uF; C_0805_2012Metric
C8: 100uF_35V; CP_Electrolytic_5x5.3
D1: LED_RED; LED_0603_1608Metric
D2, D3: SS34; D_SMA
H1, H2, H3, H4: MountingHole_M2.5
J3, J4: Conn_01x08; PinHeader_1x08_P2.54mm_Vertical
J5, J6, J7: ScrewTerm_2P; ScrewTerm-5.08-2P
J8: Conn_01x03; PinHeader_1x03_P2.54mm_Vertical
L1: 4.7uH; IND-4040
R3, R4: 5.1k; R_0603_1608Metric
R7: 10k; R_0603_1608Metric
R8: 1k; R_0603_1608Metric
R10, R11: 100k; R_0603_1608Metric
U1: ESP32-C6-WROOM-1
U2: AP2112K-3.3; SOT-23-5
U3: AP63205; SOT-23-6
X1: USB_C_16P; USB_C_Receptacle_USB2.0_16P

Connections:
+3V3: C2.1, C3.1, J3.2, J3.3, J4.7, J8.1, R7.1, R8.1, U1.2, U2.5
+5V: C6.1, D2.2, L1.2, R10.1, U2.1, U2.3, U3.5
BOOT: BT1.1, BT1.3, BT2.1, BT2.3, U1.8
BST: C7.1, U3.6
DIAG: J3.4, U1.7
DIR: J3.8, U1.5
EN: R7.2, U1.3
ENDSTOP: J8.2, U1.16
FB: R10.2, R11.1, U3.1
GND: BT1.2, BT1.4, BT2.2, BT2.4, C1.2, C2.2, C3.2, C6.2, C8.2, J4.2, J4.8, J8.3, R3.2, R4.2, R11.2, U1.1, U1.28, U1.29, U2.2, U3.2, X1.1, X1.8, X1.9, X1.16, X1.S1, X1.S2, X1.S3, X1.S4
LED1_A: D1.1, R8.2
MOT_B1: J4.4, J5.1, J6.1, J7.1
MOT_B2: J4.3, J5.2, J6.2, J7.2
STAT_LED: D1.2, U1.9
STEP: J3.7, U1.4
SW: C7.2, L1.1, U3.4
TMC_EN: J3.1, U1.6
TMC_UART: J3.6, U1.23
USB_CC1: R3.1, X1.3
USB_CC2: R4.1, X1.14
USB_DM: U1.13, X1.5, X1.12
USB_DP: U1.14, X1.4, X1.13
VBUS: C1.1, D2.1, X1.2, X1.7, X1.10, X1.15
VMOT: C8.1, D3.1, J4.1, U3.3

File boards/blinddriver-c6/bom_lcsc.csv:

ref,value,footprint,lcsc,mpn,qty
U1,ESP32-C6-WROOM-1,blinddriver-c6:ESP32-C6-WROOM-1,C5366877,ESP32-C6-WROOM-1-N8,1
X1,USB_C_16P,Connector_USB:USB_C_Receptacle_USB2.0_16P,C165948,TYPE-C-31-M-12,1
U2,AP2112K-3.3,Package_TO_SOT_SMD:SOT-23-5,C51115,AP2112K-3.3TRG1,1
U3,AP63205,Package_TO_SOT_SMD:SOT-23-6,C2071056,AP63205WU-7,1
U4,TMC2209,blinddriver-c6:TMC2209-socket,C2150710,TMC2209-LA-T,1
J3,J4,Conn_01x08,Connector_PinHeader_2.54mm:PinHeader_1x08_P2.54mm_Vertical,C492407,PZ254V-11-08P,2
J5,J6,J7,ScrewTerm_2P,blinddriver-c6:ScrewTerm-5.08-2P,C8465,WJ500V-5.08-2P,3
J8,Conn_01x03,Connector_PinHeader_2.54mm:PinHeader_1x03_P2.54mm_Vertical,C49257,KH-2.54PH180-1X3P-L13.5,1
D2,D3,SS34,Diode_SMD:D_SMA,C8678,SS34,2
C8,100uF_35V,Capacitor_SMD:CP_Electrolytic_5x5.3,C2836437,RVE100UF35V67RV0072,1
L1,4.7uH,blinddriver-c6:IND-4040,C167874,FNR4030S4R7MT,1
C6,22uF,Capacitor_SMD:C_0805_2012Metric,C45783,CL21A226MAQNNNE,1
C7,C3,100nF,Capacitor_SMD:C_0603_1608Metric,C14663,0603B104K500NT,2
R10,R11,100k,Resistor_SMD:R_0603_1608Metric,C25803,0603WAF1003T5E,2
BT1,BT2,SW_PUSH,blinddriver-c6:Tactile-6x6-SMD,C139797,TS-1187A-B-A-B,2
D1,LED_RED,LED_SMD:LED_0603_1608Metric,C2286,LTST-C190KRKT,1
R8,1k,Resistor_SMD:R_0603_1608Metric,C21190,0603WAF1001T5E,1
R3,R4,5.1k,Resistor_SMD:R_0603_1608Metric,C23186,0603WAF5101T5E,2
R7,10k,Resistor_SMD:R_0603_1608Metric,C25804,0603WAF1002T5E,1
C1,C2,10uF,Capacitor_SMD:C_0603_1608Metric,C15849,CL10A106KP8NNNC,2
